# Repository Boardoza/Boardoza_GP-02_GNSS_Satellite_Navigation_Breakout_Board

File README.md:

# Boardoza GP-02 BDS/GNSS Multi-Mode Navigation Receiver Breakout Board

The **Boardoza GP-02** is a high-performance **satellite navigation breakout board** featuring the GP-02 SOC, which supports **multi-mode positioning systems** including **BeiDou (BDS)**, **GPS**, and **GLONASS**. It is designed to provide **accurate and reliable geolocation data**, even in challenging signal environments, making it ideal for applications such as **automotive navigation**, **asset tracking**, and **outdoor robotics**.

This module offers **TTL-level UART communication**, making it easy to interface with microcontrollers, and features **low power consumption**, making it highly suitable for battery-powered systems. Its compact design and integrated RF front-end simplify integration in space-constrained projects.

## [Click here to purchase!](https://www.ozdisan.com/maker-and-iot-products/boardoza/boardoza-modules/BOARDOZA-GP-02/1206509)

|Front Side|Back Side|
|:---:|:---:|
| | |

---

## Key Features

- **Multi-Mode Satellite Support:** Simultaneous support for BeiDou, GPS, and GLONASS systems ensures broad global coverage and enhanced positioning accuracy.
- **Integrated RF Front-End:** Compact SOC design includes signal processing and antenna interface for superior reception in a small footprint.
- **Low Power Design:** Operates efficiently from 3.3V or 5V sources; ideal for portable devices.
- **Simple TTL UART Communication:** Easily integrates with microcontrollers for real-time geolocation data exchange.
- **Mode Selection via Jumper Pins:** Configure BDS+GPS or GPS+GLONASS modes via J4 jumper configuration.

---

## Technical Specifications

**Model:** Ai Thinker GP-02  
**Voltage Input Type:** 4-pin 2.50mm header  
**Input Voltage:** 5V or 1S Li-Ion Battery (3.3V)  
**Functions:** BDS/GNSS Multi-Mode Navigation Receiver SOC  
**Communication Interface:** UART (TTL Level)  
**Connector Voltage Level:** 3.3V (J3, J4)  
**Operating Temperature:** -40°C ~ +85°C  
**Board Dimensions:** 20mm x 40mm  

---

## Board Pinout

### ( J1 ) UART Communication & Power

| Pin Number | Pin Name | Description            |
|:----------:|:--------:|------------------------|
| 1          | VCC      | Power Supply           |
| 2          | RX       | Received Data Pin      |
| 3          | TX       | Transmitted Data Pin   |
| 4          | GND      | Ground                 |

### ( J3 ) GNSS Control & Timing

| Pin Number | Pin Name | Description                                   |
|:----------:|:--------:|-----------------------------------------------|
| 1          | PPS      | Time pulse signal output                      |
| 2          | N/F      | Shutdown control (active LOW, internal pull-up) |
| 3          | RST      | External reset input (leave unconnected)      |

### ( J4 ) GNSS System Selection Jumper

| Pin Combination | Mode          | Description |
|:---------------:|---------------|-------------|
| 1–2             | BDS + GPS     | Jumper connects IO to HIGH (via VCC) |
| 2–3             | GPS + GLONASS | Jumper connects IO to GND (LOW state) |

> **Note:** J4 is a clever use of hardware jumper to select GNSS mode. When middle pin floats (no jumper), the module defaults to BDS + GPS.

---

## Board Dimensions

---

## Compatible Antennas

For optimal satellite reception and stable positioning performance, it is strongly recommended to use a properly tuned **active GNSS antenna** compatible with the **L1 band**.

Since the GP-02 supports **GPS (1575.42 MHz L1), BeiDou B1 (1561.098 MHz), and GLONASS L1 (~1602 MHz)**, the antenna must cover the **1559–1606 MHz frequency range** to ensure reliable multi-constellation tracking.

An active antenna with an integrated **Low Noise Amplifier (LNA)** significantly improves signal acquisition time, enhances positioning accuracy, and maintains stable performance in weak-signal environments such as urban areas, dense foliage, or partially obstructed outdoor spaces.

Using a properly matched antenna also reduces signal loss and improves receiver sensitivity.

[Recommended Antenna: Active GNSS L1 Antenna (GPS / BDS / GLONASS)  3V–5V with SMA Connector](https://www.ozdisan.com/p/rf-antenler-660/sunnyway-rf-swg003-sw19019ib93-1207541)

**Key Antenna Characteristics:**

- **Frequency Range:** 1559–1606 MHz (L1 Band)  
- **Center Frequencies:** 1.559 / 1.575 / 1.602 GHz  
- **Gain:** 2.13 dBi (1561 MHz), 2.11 dBi (1575 MHz), 2.91 dBi (1602 MHz)   
- **GNSS Support:** GPS, BeiDou, GLONASS, GALILEO
- **Type:** Active patch antenna with integrated LNA
- **Operating Voltage:** 3V–5V (bias powered)
- **Connector Type:** IPEX MHF1
- **Impedance:** 50Ω

>  **Important:** Always connect the antenna before powering the module. Operating the GNSS receiver without a connected antenna may degrade RF performance and potentially damage the RF front-end.

---

## Step Files

[Boardoza GP-02.step](./assets/Boardoza%20GP-02%20Step.step)

---

## Datasheet

[Boardoza GP-02 Datasheet.pdf](./assets/GP-02%20Datasheet.pdf)

---

## Version History

- V1.0.0 - Initial Release

---

## Support

- If you have any questions or need support, please contact <support@boardoza.com>

---

## License

Shield: [![CC BY-SA 4.0][cc-by-sa-shield]][cc-by-sa]

This work is licensed under a [Creative Commons Attribution-ShareAlike 4.0 International License][cc-by-sa].

[![CC BY-SA 4.0][cc-by-sa-image]][cc-by-sa]

[cc-by-sa]: http://creativecommons.org/licenses/by-sa/4.0/
[cc-by-sa-image]: https://licensebuttons.net/l/by-sa/4.0/88x31.png
[cc-by-sa-shield]: https://img.shields.io/badge/License-CC%20BY--SA%204.0-lightgrey.svg

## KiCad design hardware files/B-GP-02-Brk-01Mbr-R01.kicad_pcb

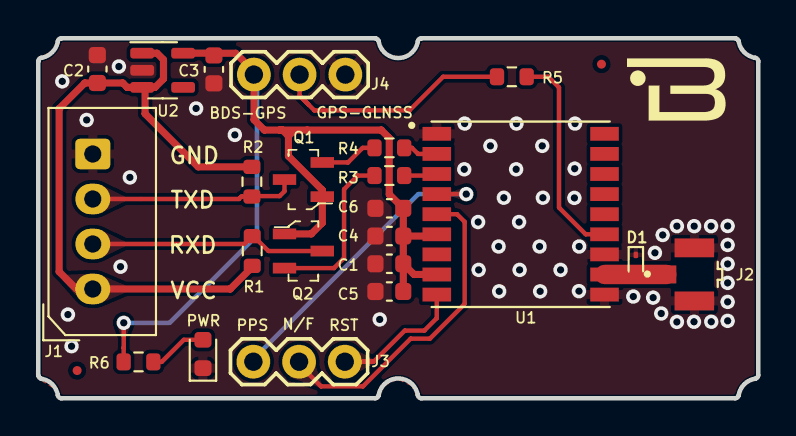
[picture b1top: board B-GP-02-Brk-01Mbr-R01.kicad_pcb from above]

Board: 2 copper layers, 40.0 x 20.0 mm, 22 parts (0 on the bottom side), 16 nets.

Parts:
C1, C2, C3: 1uF; C_0603_1608Metric
C4: 820pF; C_0603_1608Metric
C5: 10uF; C_0603_1608Metric
C6: 100nF; C_0603_1608Metric
D1: SZESD9101P2T5G; D_SOD-923
J1: MOLEX_CONNECTOR_1X4; 2317-04S_1x04_P2.50mm_Vertical
J2: 321A-331251; IPEX_20279-001E-03
J3, J4: CONN_03; 1X03
PWR: LED POWER; LED_0603_1608Metric
Q1, Q2: 2N7002_R1_00001; SOT-23-3
R1, R2, R6: 10K; R_0603_1608Metric
R3, R4, R5: 22; R_0603_1608Metric
U1: GP-02; GPS-02
U2: TLV73333PDBVR; SOT-23-5

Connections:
+3V3: C1.2, C3.1, C4.2, C5.2, C6.1, J4.3, Q1.1 (G), Q2.1 (G), R6.1, U1.6 (VRTC), U1.8 (3V3), U2.5 (OUT)
GND: C1.1, C2.2, C3.2, C4.1, C5.1, C6.2, D1.1 (K), J1.4, J2.2, J2.3, J4.1, PWR.1 (K), U1.1 (GND), U1.10 (GND), U1.12 (GND), U2.2 (GND)
IO8: J4.2, R5.2
unnamed: D1.2 (A), J2.1, U1.11 (RF)
unnamed: PWR.2 (A), R6.2
unnamed: Q1.2 (S), R4.2
unnamed: Q2.2 (S), R3.1
unnamed: R5.1, U1.13 (IO8)
unnamed: R3.2, U1.3 (RX0)
unnamed: R4.1, U1.2 (TX0)
N/F: J3.2, U1.5 (N/F)
PPS: J3.1, U1.4 (PPS)
RST: J3.3, U1.9 (RST)
RXD: J1.2, Q2.3 (D), R1.2
TXD: J1.3, Q1.3 (D), R2.2
VCC: C2.1, J1.1, R1.1, R2.1, U2.1 (IN), U2.3 (EN)

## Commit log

2024-08-29 Initial commit for GP-02 breakout board.
2024-12-23 Add Gerber and Hardware Design files for GP-02 breakout board.
2024-12-23 Update README.md to enhance product description and clarify specifications for GP-02 breakout board
2024-12-23 Update links in README.md to point to correct asset locations for step file and datasheet
2025-03-25 Add GP-02 library
2025-10-31 Rename STEP model to match asset naming
2026-02-17 Update README.md
    Add Compatible Antennas
